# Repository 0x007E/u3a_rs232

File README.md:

# `U3A_rs232` - RS232 - Adapter for U3A

The `U3A_rs232` project is based on a ([MAX3232](#additional-information)) that ist used to change the TTL/CMOS level to the required level of TIA/EIA-232-F standard. It can simply be adapted to the [U3A-Module](https://github.com/0x007e/u3a). The Module can be used with a [DSUB](https://www.reichelt.de/de/de/shop/produkt/d-sub-stecker_9-pol_flachbandkabel_ohne_isolator-6987) connector.

> To use it with a [DSUB](https://www.reichelt.de/de/de/shop/produkt/d-sub-stecker_9-pol_flachbandkabel_ohne_isolator-6987) connector it is necessary to create a connector cable that can be plugged into the IDC connector.

| Experience | Level |
|:------------|:-----:|
| Soldering   |  |
| Mechanical  |  |

# Downloads

| Type      | File               | Description              |
|:---------:|:------------------:|:-------------------------|
| Schematic | [pdf](https://github.com/0x007E/u3a_rs232/releases/latest/download/schematic.pdf) / [cadlab](https://cadlab.io/project/29701/main/files) | Schematic files |
| Board | [pdf](https://github.com/0x007E/u3a_rs232/releases/latest/download/pcb.pdf) / [cadlab](https://cadlab.io/project/29701/main/files) | Board file |
| Drill | [pdf](https://github.com/0x007E/u3a_rs232/releases/latest/download/drill.pdf) | Drill file |
| BoM | [xlsx](https://github.com/0x007E/u3a_rs232/releases/latest/download/bom.xlsx) / [html](https://github.com/0x007E/u3a_rs232/releases/latest/download/ibom.html)          | Bill of Material as Excel/interactive HTML |
| PCB    | [zip](https://github.com/0x007E/u3a_rs232/releases/latest/download/kicad.zip) / [tar](https://github.com/0x007E/u3a_rs232/releases/latest/download/kicad.tar.gz)    | KiCAD/Gerber/BoM/Drill files       |
| Mechanical | [zip](https://github.com/0x007E/u3a_rs232/releases/latest/download/freecad.zip) / [tar](https://github.com/0x007E/u3a_rs232/releases/latest/download/freecad.tar.gz) | FreeCAD/Housing and PCB (STEP/STL) files     |

# Hardware

There are two parts of the hardware. The pcb and the housing of the `U3A_rs232`. The pcb is created with [KiCAD](#additional-information) and the housing with [FreeCAD](#additional-information). All files are built with `github actions` so that they are ready for a production environment. The housing is printed with a 3D-printer (`Dremel 3D40`).

## PCB

The circuit board is populated on both sides (Top, Bottom). The best way for soldering the `SMD` components is within a vapor phase soldering system and for the `THT` components with a standard soldering system.

### Top Layer

### Bottom Layer

## Mechanical

The housing has a tolerance of `0.2mm` on each side of the case. So the pcb should fit perfectly in the housing. The tolerance can be modified with `FreeCAD` in the `Parameter` Spreadsheet.

### Assembled

#### Exploded

# Connection/Setup

The `U3A_rs232` is powerd over the `U3A` board with `5V`. The voltage of the pins are driven by a `MAX3232` that creates its own voltage for data transmission that meets the TIA/EIA-232-F standard.

## Simple loopback setup for testing purpose

``` bash
#
#            +--------------------------------+           +-----------------------------------+      +---------------------+
#            |                              J2|           |J2     U                       +---+---+  |                     |
#            | J1         U3A_rs232        +--+--+     +--+--+    S                U      |  USB  |--+ +-----------------+ |
#         +--+--+                          | VCC +-----+ VCC |    B      UPDI      3      +---+---+  | | TeraTerm        | |
#         + GND | (5)                      | GND +-----+ GND |    /    +---+---+   A          |      | | ~~~~~~~~        | |
#         +-----+                          |  X  +-----| PDI |    U    |   |   |              |      | | ~~~~~           | |
#   L     + CTS | (8)                      | CTS +-----+ CTS |    A    |   |   |              |      | | ~~~~~~~~~~~~    | |
#   O     + RTS | (7)                      | RTS +-----+ RTS |    R    | X | X |              |      | |                 | |
#   O +---+ TXD | (3)                      | TXD +-----+ TXD |    T    +---+---+     +-+      |      | +-----------------+ |
#   P +---+ RXD | (2)                      | RXD +-----+ RXD |    /                 / /       |      |                     |
#   B     +--+--+                          +--+--+     +--+--+    U               +-+-+-+-+-+-+      | Computer            |
#   A        |                                |           |       P               | 5V  | 3V3 |      |                     |
#   C        |                                |           |       D               +-----+-----+      +---------------------+
#   K        |                                |           |       I         J4                |
#            |                                |           | +---+---+---+---+---+---+---+---+ |
#            |                                |           | | V | C | C | D | D | D | R | G | |
#            |                                |           +-+ C | B | B | C | T | C | I | N +-+
#            |                                |             | C | 3 | 2 | D | R | R |   | D |
#            +--------------------------------+             +---+---+---+---+---+---+---+---+
```

# Additional Information

| Type       | Link                                                     | Description                                          |
|:----------:|:--------------------------------------------------------:|:-----------------------------------------------------|
| MAX3232    | [pdf](https://www.ti.com/lit/ds/symlink/max3232e-q1.pdf) | UART / RS232 level converter                         |
| KiCAD      | [web](https://www.kicad.org/)                            | KiCAD project page                                   |
| FreeCAD    | [web](https://www.freecad.org/)                          | FreeCAD project page                                 |

---

R. GAECHTER

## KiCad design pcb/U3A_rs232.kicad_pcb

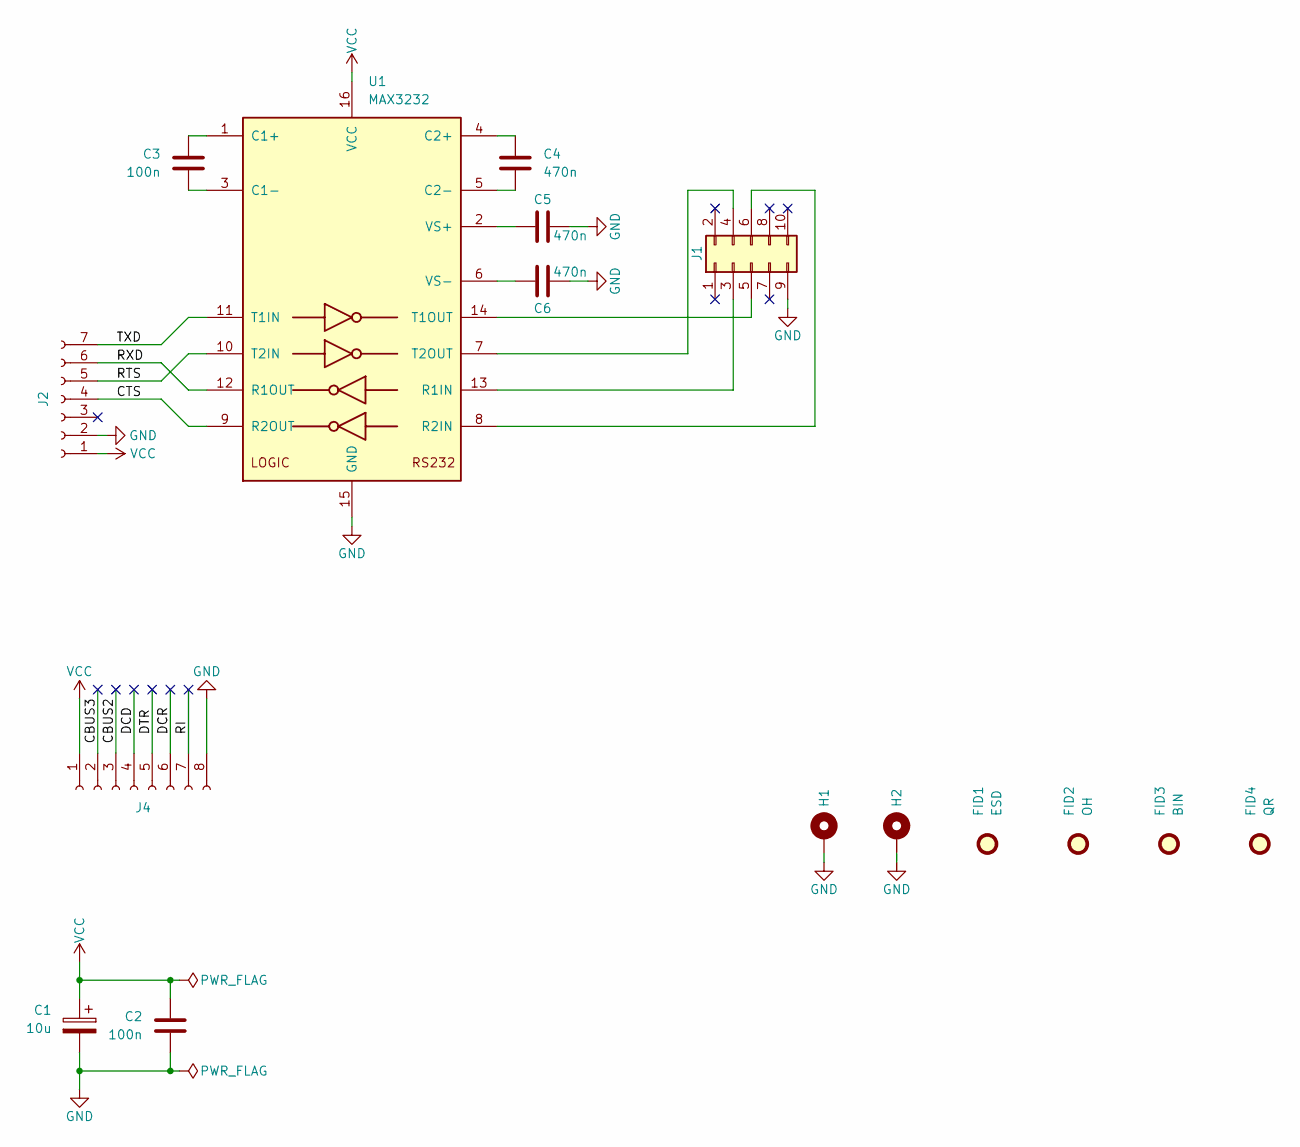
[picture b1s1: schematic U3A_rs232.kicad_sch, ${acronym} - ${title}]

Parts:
C1: 10u; CP_EIA-6032-28_Kemet-C
C2, C3: 100n; C_1206_3216Metric
C4, C5, C6: 470n; C_1206_3216Metric
FID1: ESD; ESD-Logo_6.6x6mm_SilkScreen
FID2: OH; OSHW-Logo_5.7x6mm_SilkScreen
FID3: BIN; WEEE-Logo_4.2x6mm_SilkScreen
FID4: QR; QR_0x007e
H1, H2: MountingHole_Pad; MountingHole_2.7mm_M2.5_Pad; DigiKey 732-12987-ND
J1: Conn_02x05_Odd_Even; IDC-Header_2x05_P2.54mm_Vertical
J2: Conn_01x07_Socket; PinSocket_1x07_P2.54mm_Vertical
J4: Conn_01x08_Socket; PinSocket_1x08_P2.54mm_Vertical
U1: MAX3232; TSSOP-16_4.4x5mm_P0.65mm

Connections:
/CBUS2: J4.3
/CBUS3: J4.2
/CTS: J2.4, U1.9 (R2OUT)
/DCD: J4.4
/DCR: J4.6
/DTR: J4.5
/RI: J4.7
/RTS: J2.5, U1.10 (T2IN)
/RXD: J2.6, U1.12 (R1OUT)
/TXD: J2.7, U1.11 (T1IN)
GND: C1.2, C2.1, C5.1, C6.1, H1.1, H2.1, J1.9, J2.2, J4.8, U1.15 (GND)
unnamed: J1.3, U1.13 (R1IN)
unnamed: J1.4, U1.7 (T2OUT)
unnamed: J1.5, U1.14 (T1OUT)
unnamed: J1.6, U1.8 (R2IN)
unnamed: C3.2, U1.1 (C1+)
unnamed: C3.1, U1.3 (C1-)
unnamed: C4.2, U1.4 (C2+)
unnamed: C4.1, U1.5 (C2-)
unnamed: C5.2, U1.2 (VS+)
unnamed: C6.2, U1.6 (VS-)
VCC: C1.1, C2.2, J2.1, J4.1, U1.16 (VCC)

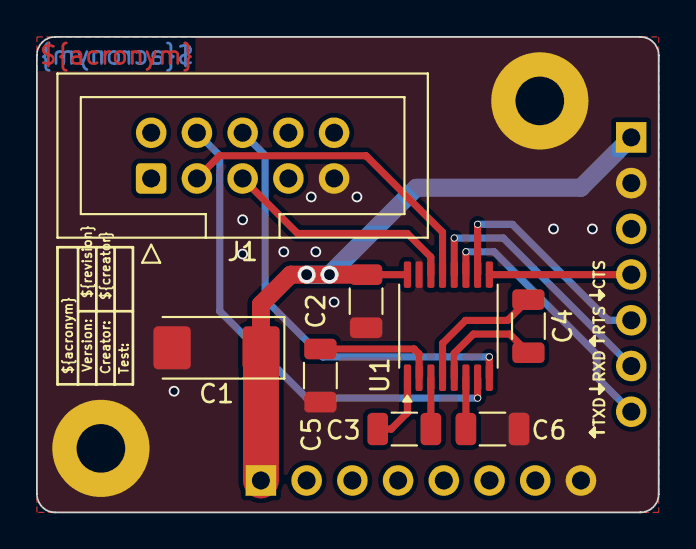
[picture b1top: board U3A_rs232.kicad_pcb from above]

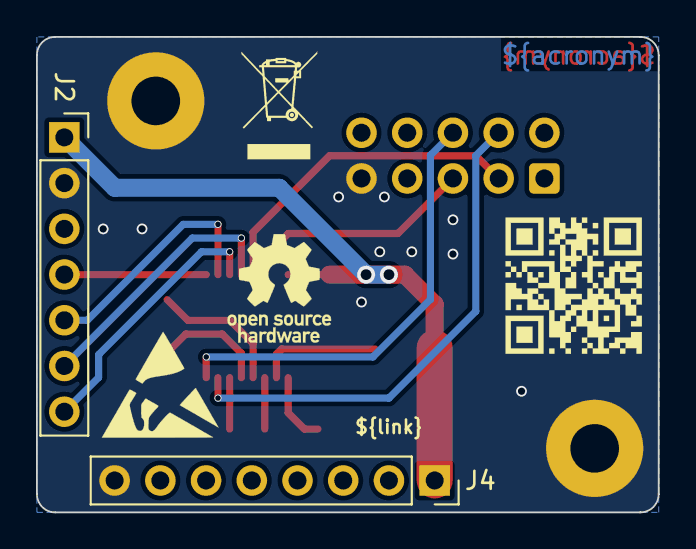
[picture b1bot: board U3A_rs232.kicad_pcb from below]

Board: 2 copper layers, 34.5 x 26.4 mm, 16 parts (6 on the bottom side), 16 nets.

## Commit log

2025-10-21 Adapt partlist vendors
2025-10-21 Fabrication layer setup
2025-10-21 Add README.md
2025-10-21 Add build pipeline
2025-10-21 Add release pipeline
2025-10-22 Adapt screw length
2025-11-23 Fix connection setup ascii graphic
2025-11-23 Text refactoring
2025-11-25 Add deepwiki badge
2026-06-20 Update to KiCAD 9
2026-06-20 Rename/Add/Remove bom fields
2026-06-20 Update build pipeline
2026-06-20 Update release pipeline
2026-06-20 Rearrange rs232 traces
2026-06-22 Adapt output filenames
2026-06-22 Add missing values in bom
2026-06-22 Adapt config and update action versions
2026-06-22 Fix freecad path issue

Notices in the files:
README.md:
License CC By-NC-SA
parts and their libraries:
license: CC BY-NC-SA 4.0
